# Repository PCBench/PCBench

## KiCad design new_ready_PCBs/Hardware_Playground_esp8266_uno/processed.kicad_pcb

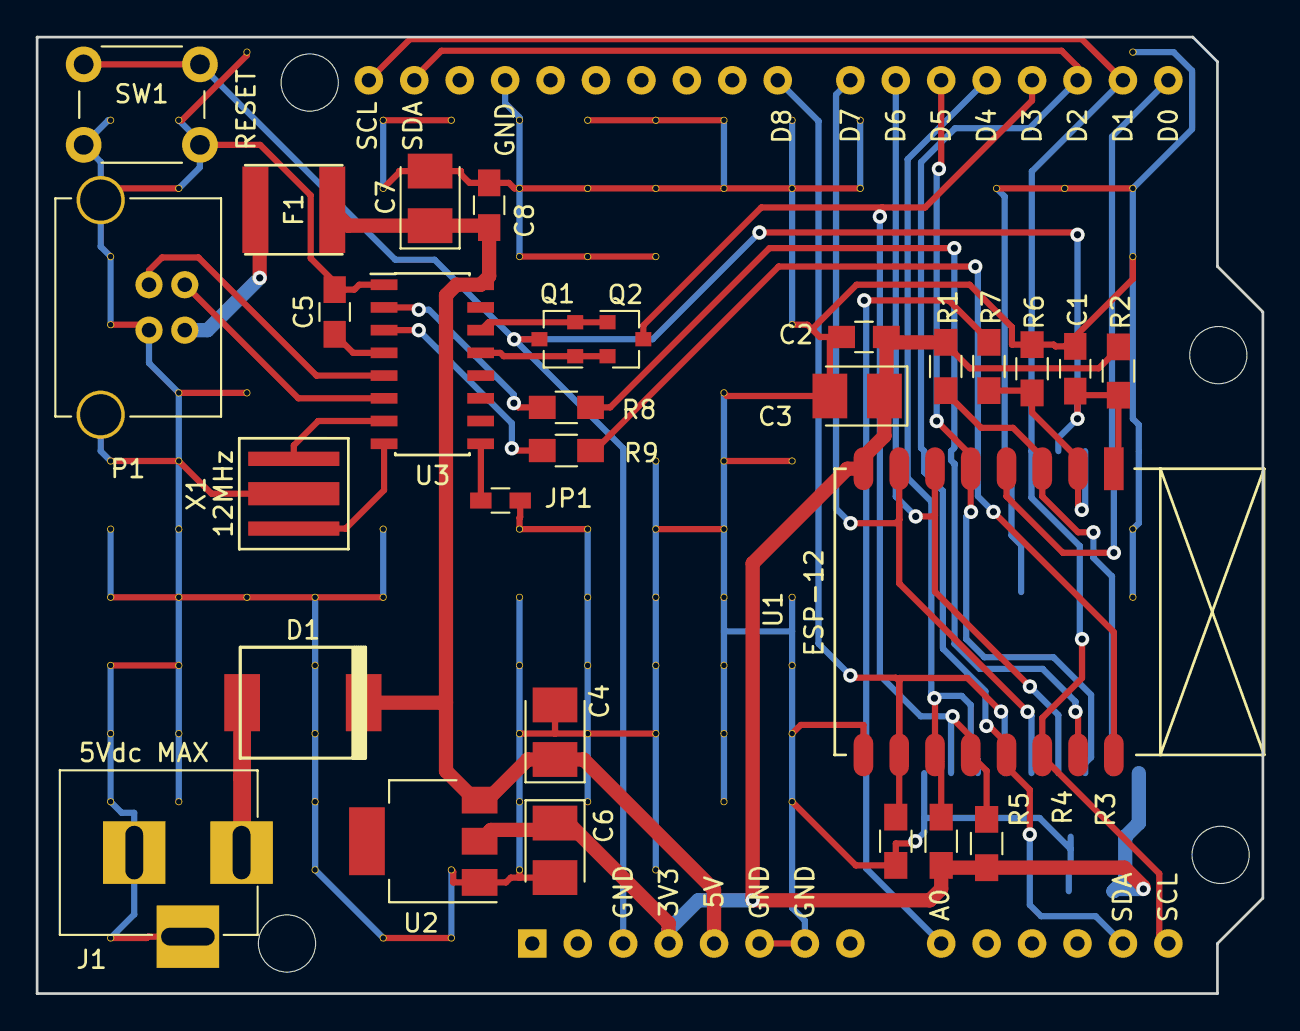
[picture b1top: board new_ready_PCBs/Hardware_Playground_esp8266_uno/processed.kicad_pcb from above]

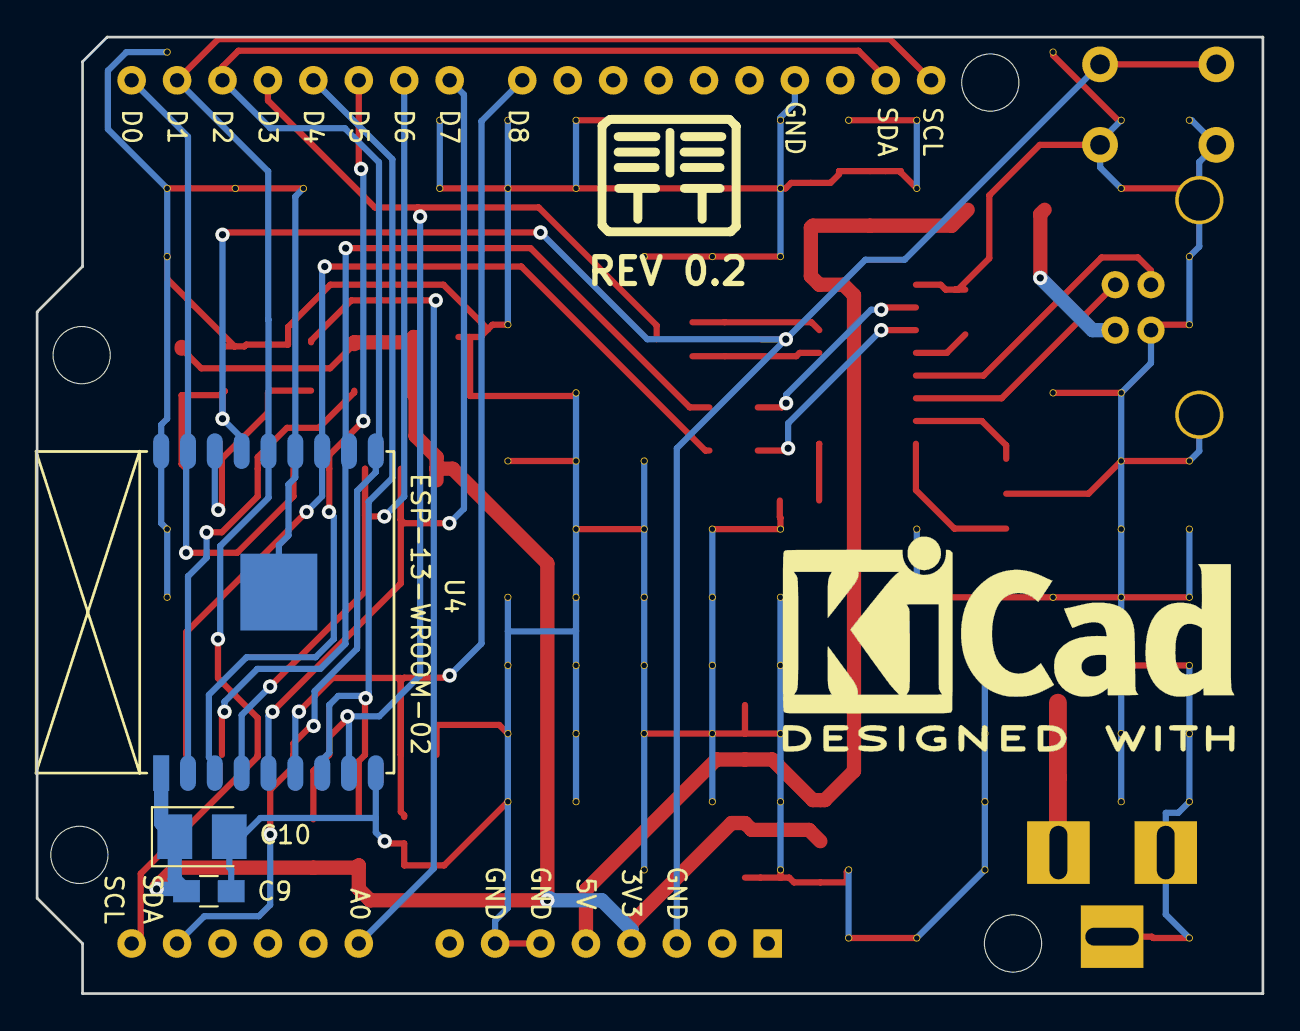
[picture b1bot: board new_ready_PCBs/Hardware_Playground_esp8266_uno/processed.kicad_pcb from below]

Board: 2 copper layers, 68.5 x 53.5 mm, 120 parts (4 on the bottom side), 30 nets.

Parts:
A1: Arduino_UNO_R3
C1, C2, C8, C9: 100n; C_0805_HandSoldering
C3, C7, C10: 10u; CP_Tantalum_Case-B_EIA-3528-21_Reflow
C4, C6: 22u; CP_Tantalum_Case-B_EIA-3528-21_Reflow
C5: 10n; C_0805_HandSoldering
D1: SS34; do214ab
F1: MF-SMDF050; mf-smdf050
J1: Barrel_Jack; BARREL_JACK
JP1: CTS; R_0603_HandSoldering
P1: USB; USB_B
Q1, Q2: 2N2222; SOT-23
R1, R2, R3, R4, R5: 10K; R_0805_HandSoldering
R6: 100K; R_0805_HandSoldering
R7: 220K; R_0805_HandSoldering
R8, R9: 470; R_0805_HandSoldering
SW1: RESET; SW_PUSH_6mm
U1: ESP-12
U2: AMS1117-3.3; SOT-223
U3: CH340G; SOIC-16_3.9x9.9mm_Pitch1.27mm
U4: ESP-13-WROOM-02
V3_2, V3_4, V3_5, V3_7, V3_8, V3_9, V3_10, V3_11, V3_12, V3_14, V4_2, V4_3, V4_6, V4_7, V4_8, V4_9, V4_10, V4_11, V4_12, V5_1, V5_6, V5_9, V6_9, V6_10, V6_11, V6_12, V6_13, V7_2, V7_3, V7_8, V7_9, V7_14, V8_2, V8_13, V8_14, V9_2, V9_3, V9_4, V9_8, V9_9, V9_10, V9_11, V9_12, V9_13, V10_2, V10_3, V10_4, V10_8, V10_9, V10_10, V10_11, V10_12, V11_2, V11_3, V11_4, V11_7, V11_8, V11_9, V11_10, V11_11, V11_13, V12_2, V12_3, V12_6, V12_7, V12_8, V12_9, V12_10, V12_11, V12_12, V13_2, V13_3, V13_5, V13_7, V13_9, V13_10, V13_11, V13_12, V14_2, V14_3, V16_3, V17_3, V18_1, V18_3, V18_4, V18_8, V18_9: AUTO_VIA; VIA_MATRIX
X1: 12MHz; ZTTCS-3

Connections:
+3V3: A1.4, C2.2, C3.1, C6.1, C9.2, C10.1, R1.2, R2.2, R3.2, R4.2, U1.8, U2.2, U4.1
+5V: A1.5, C4.1, C7.1, C8.2, D1.1, F1.1, U2.3, U3.16
/A0: A1.9, R7.1
/ADC: R6.1, R7.2, U1.2, U4.16
/DTR: Q1.1, Q2.2, U3.13
/EN: R1.1, U1.3, U4.2
/GPIO0: A1.18, Q2.3, R3.1, U1.12, U4.8
/GPIO2: A1.19, R4.1, U1.11, U4.7
/GPIO4: A1.13, A1.17, A1.31, U1.13, U4.10
/GPIO5: A1.14, A1.16, A1.32, U1.14, U4.14
/GPIO12: A1.21, U1.6, U4.4
/GPIO13: A1.22, U1.7, U4.5
/GPIO14: A1.20, U1.5, U4.3
/GPIO15: A1.23, R5.1, U1.10, U4.6
/GPIO16: A1.15, U1.4, U4.17
/RESET: A1.3, C1.2, Q1.3, R2.1, SW1.1, U1.1, U4.15
/RTS: Q1.2, Q2.1, U3.14
/RX: R8.2, U1.15, U4.11
/TX: R9.2, U1.16, U4.12
GND: A1.6, A1.7, A1.29, C1.1, C2.1, C3.2, C4.2, C5.2, C6.2, C7.2, C8.1, C9.1, C10.2, J1.2, J1.3, JP1.1, P1.4, P1.5, R5.2, R6.2, SW1.2, U1.9, U2.1, U3.1, U4.9, U4.13, U4.18, U4.PAD, V3_2.1, V3_4.1, V3_5.1, V3_7.1, V3_8.1, V3_9.1, V3_10.1, V3_11.1, V3_12.1, V3_14.1, V4_2.1, V4_3.1, V4_6.1, V4_7.1, V4_8.1, V4_9.1, V4_10.1, V4_11.1, V4_12.1, V5_1.1, V5_6.1, V5_9.1, V6_9.1, V6_10.1, V6_11.1, V6_12.1, V6_13.1, V7_2.1, V7_3.1, V7_8.1, V7_9.1, V7_14.1, V8_2.1, V8_13.1, V8_14.1, V9_2.1, V9_3.1, V9_4.1, V9_8.1, V9_9.1, V9_10.1, V9_11.1, V9_12.1, V9_13.1, V10_2.1, V10_3.1, V10_4.1, V10_8.1, V10_9.1, V10_10.1, V10_11.1, V10_12.1, V11_2.1, V11_3.1, V11_4.1, V11_7.1, V11_8.1, V11_9.1, V11_10.1, V11_11.1, V11_13.1, V12_2.1, V12_3.1, V12_6.1, V12_7.1, V12_8.1, V12_9.1, V12_10.1, V12_11.1, V12_12.1, V13_2.1, V13_3.1, V13_5.1, V13_7.1, V13_9.1, V13_10.1, V13_11.1, V13_12.1, V14_2.1, V14_3.1, V16_3.1, V17_3.1, V18_1.1, V18_3.1, V18_4.1, V18_8.1, V18_9.1, X1.2
unnamed: C5.1, U3.4
unnamed: D1.2, J1.1
unnamed: F1.2, P1.1
unnamed: JP1.2, U3.9
unnamed: P1.2, U3.6
unnamed: P1.3, U3.5
unnamed: R8.1, U3.2
unnamed: R9.1, U3.3
unnamed: U3.7, X1.1
unnamed: U3.8, X1.3

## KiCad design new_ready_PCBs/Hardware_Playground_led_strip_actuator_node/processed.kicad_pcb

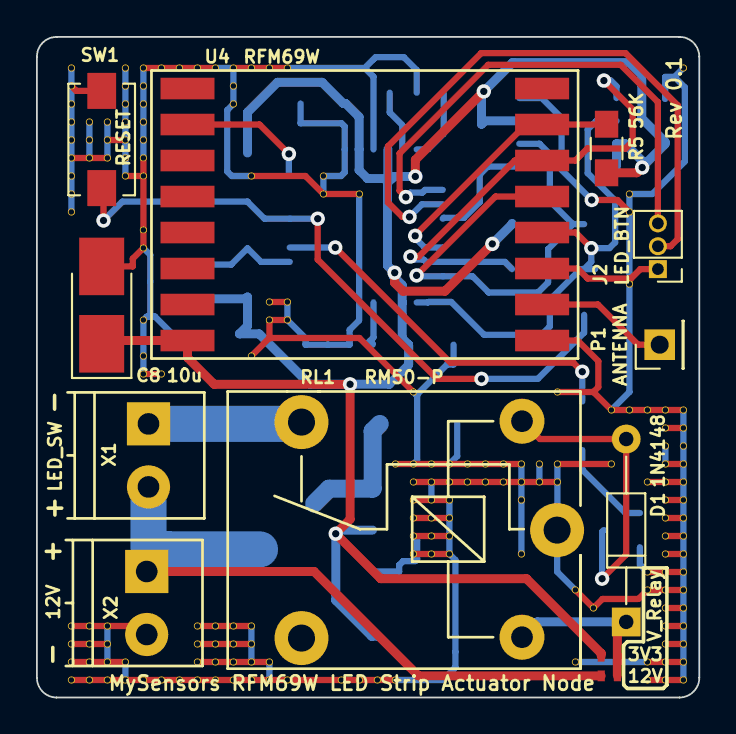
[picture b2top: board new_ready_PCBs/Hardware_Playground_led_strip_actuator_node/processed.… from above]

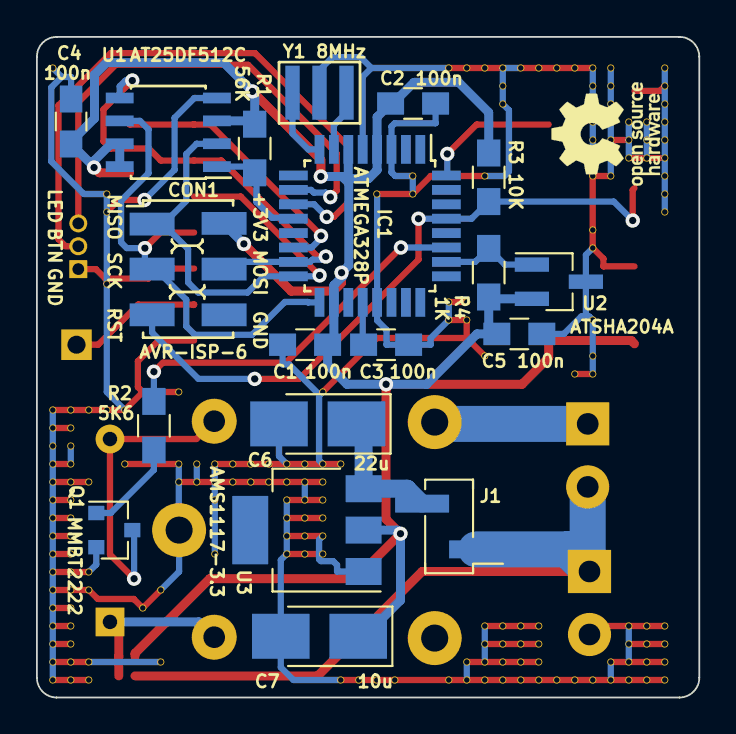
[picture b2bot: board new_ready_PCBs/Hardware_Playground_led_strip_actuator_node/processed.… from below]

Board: 2 copper layers, 36.8 x 36.7 mm, 208 parts (19 on the bottom side), 23 nets.

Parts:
C1, C2, C3, C4, C5: 100n; C_0805_HandSoldering
C6: 22u; CP_Tantalum_Case-B_EIA-3528-21_Hand
C7, C8: 10u; CP_Tantalum_Case-B_EIA-3528-21_Hand
CON1: AVR-ISP-6; AVR_ISP_SMT_Small_02x03
D1: 1N4148; D_DO-35_SOD27_P10.16mm_Horizontal
IC1: ATMEGA328P; TQFP-32_7x7mm_Pitch0.8mm
J1: EXT_DC_DC; Pin_Header_Straight_1x02_Pitch2.54mm_SMD_Pin1Left
J2: LED_BTN; Pin_Header_Straight_1x03_Pitch1.27mm
JP1: 3V3; R_0402_NoSilk
JP2: 12V; R_0402_NoSilk
P1: ANTENNA; Pin_Header_Straight_1x01_Pitch2.54mm
Q1: MMBT2222; SOT-23
R1, R5: 56K; R_0805_HandSoldering
R2: 5K6; R_0805_HandSoldering
R3: 10K; R_0805_HandSoldering
R4: 1K; R_0805_HandSoldering
RL1: RM50-P; RM50_P
SW1: RESET; SW_SPST_EVQPE1
U1: AT25DF512C; SOIC-8_3.9x4.9mm_Pitch1.27mm
U2: ATSHA204A; SOT-23_Handsoldering
U3: AMS1117-3.3; SOT-223
U4: RFM69W; RFM69HW_SMD_Handsoldering
V2_10, V2_11, V2_12, V2_13, V2_14, V2_15, V2_16, V2_17, V2_18, V2_41, V2_42, V2_43, V2_44, V3_13, V3_14, V3_15, V3_41, V3_42, V3_43, V3_44, V4_13, V4_14, V4_15, V4_41, V4_42, V4_43, V4_44, V5_10, V5_11, V5_12, V5_13, V5_14, V5_15, V5_16, V5_43, V5_44, V6_10, V6_11, V6_12, V6_13, V6_14, V6_15, V6_16, V6_19, V6_20, V6_24, V6_26, V6_27, V6_44, V7_10, V7_27, V7_44, V8_10, V8_44, V9_10, V9_41, V9_42, V9_43, V9_44, V10_10, V10_41, V10_42, V10_43, V10_44, V11_10, V11_11, V11_12, V11_41, V11_42, V11_43, V11_44, V12_10, V12_16, V12_26, V12_41, V12_42, V12_43, V12_44, V13_10, V13_23, V13_24, V13_43, V13_44, V14_10, V14_23, V14_24, V14_44, V16_16, V16_17, V17_44, V18_17, V18_44, V19_44, V20_32, V20_44, V21_28, V21_32, V21_33, V21_34, V21_35, V21_36, V21_37, V22_32, V22_33, V22_34, V22_35, V22_36, V22_37, V23_32, V23_33, V23_34, V23_35, V23_36, V23_37, V24_32, V24_33, V25_32, V25_33, V26_32, V26_33, V27_32, V27_33, V27_34, V27_37, V28_32, V28_33, V29_28, V29_32, V29_33, V30_39, V30_43, V31_40, V32_29, V32_32, V33_17, V33_18, V33_22, V33_29, V34_29, V34_33, V34_38, V34_39, V34_43, V34_44, V35_29, V35_30, V35_31, V35_32, V35_33, V35_34, V35_35, V35_36, V35_37, V35_38, V35_39, V35_40, V35_41, V35_42, V35_43, V35_44, V36_10, V36_29, V36_30, V36_31, V36_32, V36_33, V36_34, V36_35, V36_36, V36_37, V36_38, V36_39, V36_40, V36_41, V36_42, V36_43, V36_44: AUTO_VIA; VIA_MATRIX
X1: LED_SW; TerminalBlock_Pheonix_PT-3.5mm_2pol
X2: 12V; TerminalBlock_Pheonix_PT-3.5mm_2pol
Y1: 8MHz; ZTTCR-3

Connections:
+3V3: C1.2, C2.2, C4.1, C5.1, C7.1, C8.1, CON1.2, IC1.4, IC1.6, IC1.18, JP1.1, R1.2, R3.1, R4.2, R5.2, U1.3, U1.7, U1.8, U2.2, U3.2, U4.8
/ATSHA204A: IC1.26, R4.1, U2.1
/LED_12V: J1.1, JP2.2, X1.2, X2.1
/LED_BTN: IC1.11, J2.2
/LED_BTN_SIGNALING: IC1.10, J2.3
/LED_RELAY_CMD: IC1.27, R2.2
/MISO: CON1.1, IC1.16, U1.2, U4.13
/MOSI: CON1.4, IC1.15, U1.5, U4.14
/RFM69W_INT: IC1.32, U4.2
/RFM69W_SS: IC1.14, R5.1, U4.15
/RST: CON1.5, IC1.29, R3.2, SW1.1
/SCK: CON1.3, IC1.17, U1.6, U4.12
/SPI_FLASH_SS: IC1.12, R1.1, U1.1
GND: C1.1, C2.1, C3.1, C4.2, C5.2, C6.2, C7.2, C8.2, IC1.3, IC1.5, IC1.21, J2.1, Q1.2, RL1.11, SW1.2, U1.4, U2.3, U3.1, U4.9, U4.11, V2_10.1, V2_11.1, V2_12.1, V2_13.1, V2_14.1, V2_15.1, V2_16.1, V2_17.1, V2_18.1, V2_41.1, V2_42.1, V2_43.1, V2_44.1, V3_13.1, V3_14.1, V3_15.1, V3_41.1, V3_42.1, V3_43.1, V3_44.1, V4_13.1, V4_14.1, V4_15.1, V4_41.1, V4_42.1, V4_43.1, V4_44.1, V5_10.1, V5_11.1, V5_12.1, V5_13.1, V5_14.1, V5_15.1, V5_16.1, V5_43.1, V5_44.1, V6_10.1, V6_11.1, V6_12.1, V6_13.1, V6_14.1, V6_15.1, V6_16.1, V6_19.1, V6_20.1, V6_24.1, V6_26.1, V6_27.1, V6_44.1, V7_10.1, V7_27.1, V7_44.1, V8_10.1, V8_44.1, V9_10.1, V9_41.1, V9_42.1, V9_43.1, V9_44.1, V10_10.1, V10_41.1, V10_42.1, V10_43.1, V10_44.1, V11_10.1, V11_11.1, V11_12.1, V11_41.1, V11_42.1, V11_43.1, V11_44.1, V12_10.1, V12_16.1, V12_26.1, V12_41.1, V12_42.1, V12_43.1, V12_44.1, V13_10.1, V13_23.1, V13_24.1, V13_43.1, V13_44.1, V14_10.1, V14_23.1, V14_24.1, V14_44.1, V16_16.1, V16_17.1, V17_44.1, V18_17.1, V18_44.1, V19_44.1, V20_32.1, V20_44.1, V21_28.1, V21_32.1, V21_33.1, V21_34.1, V21_35.1, V21_36.1, V21_37.1, V22_32.1, V22_33.1, V22_34.1, V22_35.1, V22_36.1, V22_37.1, V23_32.1, V23_33.1, V23_34.1, V23_35.1, V23_36.1, V23_37.1, V24_32.1, V24_33.1, V25_32.1, V25_33.1, V26_32.1, V26_33.1, V27_32.1, V27_33.1, V27_34.1, V27_37.1, V28_32.1, V28_33.1, V29_28.1, V29_32.1, V29_33.1, V30_39.1, V30_43.1, V31_40.1, V32_29.1, V32_32.1, V33_17.1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
unnamed: C3.2, IC1.20
unnamed: C6.1, J1.2, U3.3
unnamed: D1.1, JP1.2, JP2.1, RL1.A1
unnamed: D1.2, Q1.3, RL1.A2
unnamed: IC1.7, Y1.3
unnamed: IC1.8, Y1.1
unnamed: P1.1, U4.10
unnamed: Q1.1, R2.1
unnamed: RL1.14, X1.1

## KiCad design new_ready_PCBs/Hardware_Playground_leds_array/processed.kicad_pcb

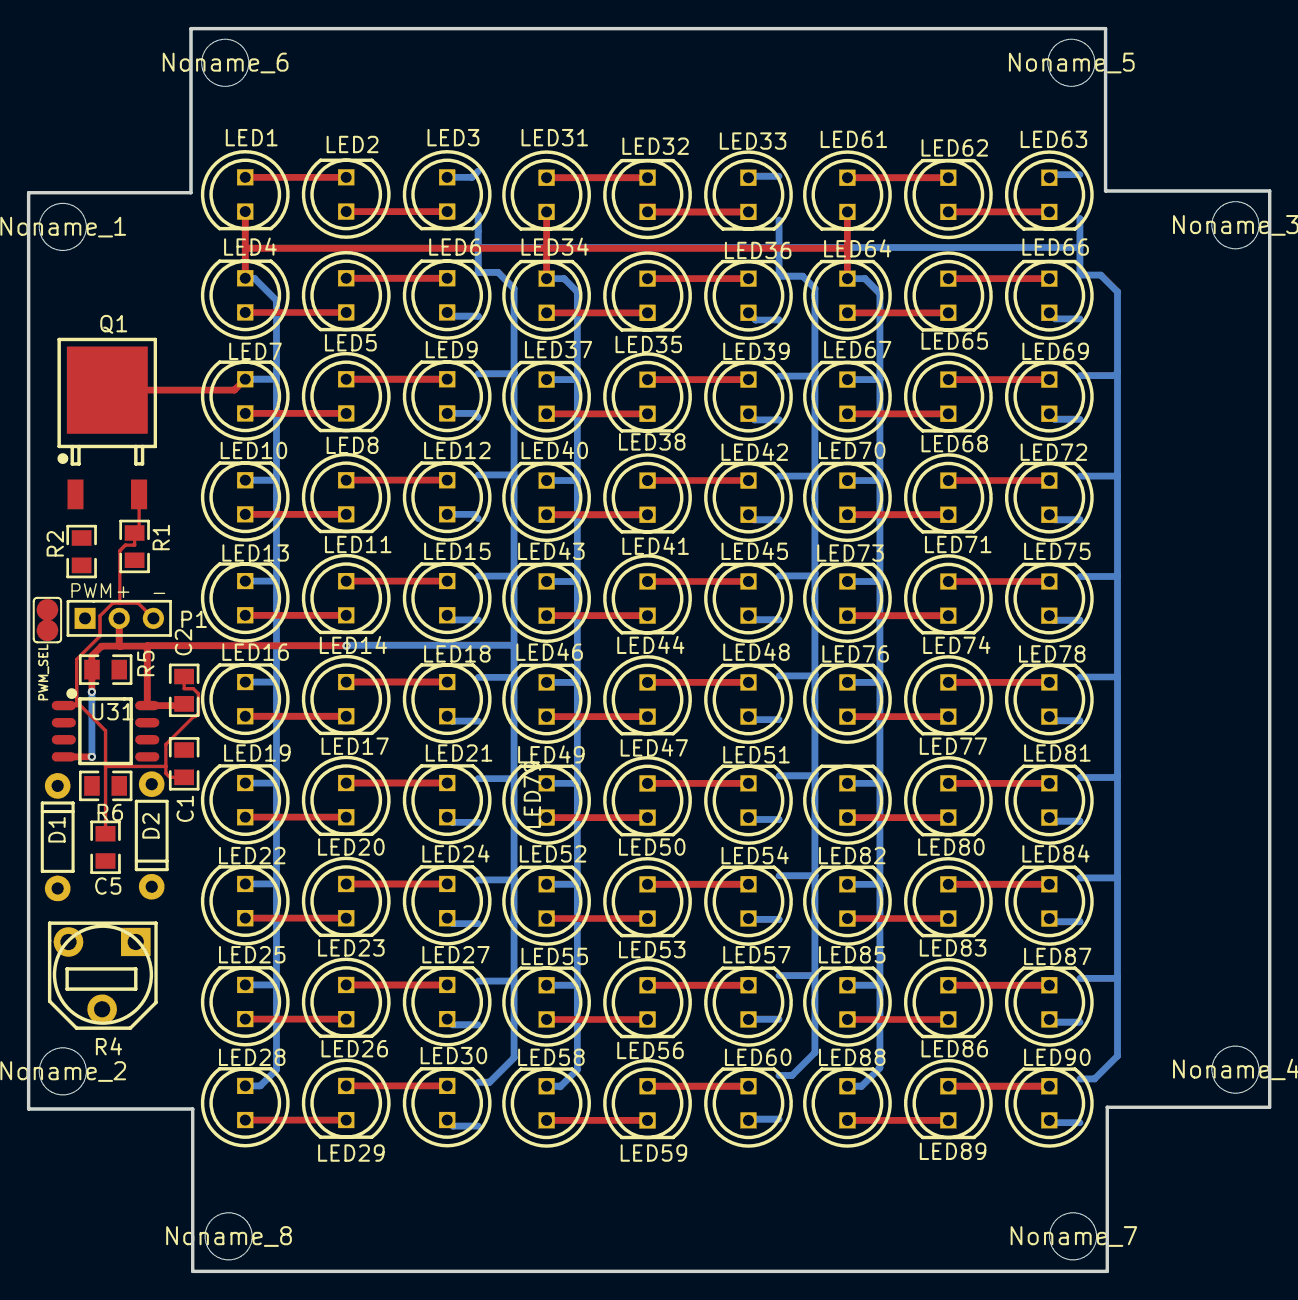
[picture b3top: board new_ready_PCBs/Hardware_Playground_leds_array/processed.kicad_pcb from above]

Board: 2 copper layers, 92.2 x 92.3 mm, 142 parts (0 on the bottom side), 93 nets.

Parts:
C1, C2: 100n; 0805
C5: 1n; 0805
D1, D2: 1N4148TA; DO-35
LED1, LED2, LED3, LED4, LED5, LED6, LED7, LED8, LED9, LED10, LED11, LED12, LED13, LED14, LED15, LED16, LED17, LED18, LED19, LED20, LED21, LED22, LED23, LED24, LED25, LED26, LED27, LED28, LED29, LED30, LED31, LED32, LED33, LED34, LED35, LED36, LED37, LED38, LED39, LED40, LED41, LED42, LED43, LED44, LED45, LED46, LED47, LED48, LED49, LED50, LED51, LED52, LED53, LED54, LED55, LED56, LED57, LED58, LED59, LED60, LED61, LED62, LED63, LED64, LED65, LED66, LED67, LED68, LED69, LED70, LED71, LED72, LED73, LED74, LED75, LED76, LED77, LED78, LED79, LED80, LED81, LED82, LED83, LED84, LED85, LED86, LED87, LED88, LED89, LED90: 5AG3HT01 280-450; LED-5MM
Noname_1, Noname_2, Noname_3, Noname_4, Noname_5, Noname_6, Noname_7, Noname_8: MountingHole_3.50mm
P1: Header-Female-2.54_1x3; HDR-3X1_2.54
PWM_SEL: SJ
Q1: IRLR024NTRPBF; TO-252-2
R1: 10K; 0805
R2: 100; 0805
R4: 10K; RM065-V1
R5, R6: 1K; 0805
U1, U2, U3, U4, U5, U6, U7, U8, U9, U10, U11, U12, U13, U14, U15, U16, U17, U18, U19, U20, U21, U22, U23, U24, U25, U26, U27, U28, U29, U30: NSI45020T1G; SOD-123F
U31: NE555G-S08-R; SOP-8_150MIL

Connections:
A: C2.1, P1.2, R5.2, U1.1, U2.1, U3.1, U4.1, U5.1, U6.1, U7.1, U8.1, U9.1, U10.1, U11.1, U12.1, U13.1, U14.1, U15.1, U16.1, U17.1, U18.1, U19.1, U20.1, U21.1, U22.1, U23.1, U24.1, U25.1, U26.1, U27.1, U28.1, U29.1, U30.1, U31.4, U31.8
GND: C1.1, C2.2, C5.1, P1.3, Q1.3, R1.1, U31.1
K: LED1.2, LED4.2, LED7.2, LED10.2, LED13.2, LED16.2, LED19.2, LED22.2, LED25.2, LED28.2, LED31.2, LED34.2, LED37.2, LED40.2, LED43.2, LED46.2, LED49.2, LED52.2, LED55.2, LED58.2, LED61.2, LED64.2, LED67.2, LED70.2, LED73.2, LED76.2, LED79.2, LED82.2, LED85.2, LED88.2, Q1.4
LED1_1: LED1.1, LED2.2
LED2_1: LED2.1, LED3.2
LED3_1: LED3.1, U1.2
LED4_1: LED4.1, LED5.2
LED5_1: LED5.1, LED6.2
LED6_1: LED6.1, U2.2
LED7_1: LED7.1, LED8.2
LED8_1: LED8.1, LED9.2
LED9_1: LED9.1, U3.2
LED10_1: LED10.1, LED11.2
LED11_1: LED11.1, LED12.2
LED12_1: LED12.1, U4.2
LED13_1: LED13.1, LED14.2
LED14_1: LED14.1, LED15.2
LED15_1: LED15.1, U5.2
LED16_1: LED16.1, LED17.2
LED17_1: LED17.1, LED18.2
LED18_1: LED18.1, U6.2
LED19_1: LED19.1, LED20.2
LED20_1: LED20.1, LED21.2
LED21_1: LED21.1, U7.2
LED22_1: LED22.1, LED23.2
LED23_1: LED23.1, LED24.2
LED24_1: LED24.1, U8.2
LED25_1: LED25.1, LED26.2
LED26_1: LED26.1, LED27.2
LED27_1: LED27.1, U9.2
LED28_1: LED28.1, LED29.2
LED29_1: LED29.1, LED30.2
LED30_1: LED30.1, U10.2
LED31_1: LED31.1, LED32.2
LED32_1: LED32.1, LED33.2
LED33_1: LED33.1, U11.2
LED34_1: LED34.1, LED35.2
LED35_1: LED35.1, LED36.2
LED36_1: LED36.1, U12.2
LED37_1: LED37.1, LED38.2
LED38_1: LED38.1, LED39.2
LED39_1: LED39.1, U13.2
LED40_1: LED40.1, LED41.2
LED41_1: LED41.1, LED42.2
LED42_1: LED42.1, U14.2
LED43_1: LED43.1, LED44.2
LED44_1: LED44.1, LED45.2
LED45_1: LED45.1, U15.2
LED46_1: LED46.1, LED47.2
LED47_1: LED47.1, LED48.2
LED48_1: LED48.1, U16.2
LED49_1: LED49.1, LED50.2
LED50_1: LED50.1, LED51.2
LED51_1: LED51.1, U17.2
LED52_1: LED52.1, LED53.2
LED53_1: LED53.1, LED54.2
LED54_1: LED54.1, U18.2
LED55_1: LED55.1, LED56.2
LED56_1: LED56.1, LED57.2
LED57_1: LED57.1, U19.2
LED58_1: LED58.1, LED59.2
LED59_1: LED59.1, LED60.2
LED60_1: LED60.1, U20.2
LED61_1: LED61.1, LED62.2
LED62_1: LED62.1, LED63.2
LED63_1: LED63.1, U21.2
LED64_1: LED64.1, LED65.2
LED65_1: LED65.1, LED66.2
LED66_1: LED66.1, U22.2
LED67_1: LED67.1, LED68.2
LED68_1: LED68.1, LED69.2
LED69_1: LED69.1, U23.2
LED70_1: LED70.1, LED71.2
LED71_1: LED71.1, LED72.2
LED72_1: LED72.1, U24.2
LED73_1: LED73.1, LED74.2
LED74_1: LED74.1, LED75.2
LED75_1: LED75.1, U25.2
LED76_1: LED76.1, LED77.2
LED77_1: LED77.1, LED78.2
LED78_1: LED78.1, U26.2
LED79_1: LED79.1, LED80.2
LED80_1: LED80.1, LED81.2
LED81_1: LED81.1, U27.2
LED82_1: LED82.1, LED83.2
LED83_1: LED83.1, LED84.2
LED84_1: LED84.1, U28.2
LED85_1: LED85.1, LED86.2
LED86_1: LED86.1, LED87.2
LED87_1: LED87.1, U29.2
LED88_1: LED88.1, LED89.2
LED89_1: LED89.1, LED90.2
LED90_1: LED90.1, U30.2

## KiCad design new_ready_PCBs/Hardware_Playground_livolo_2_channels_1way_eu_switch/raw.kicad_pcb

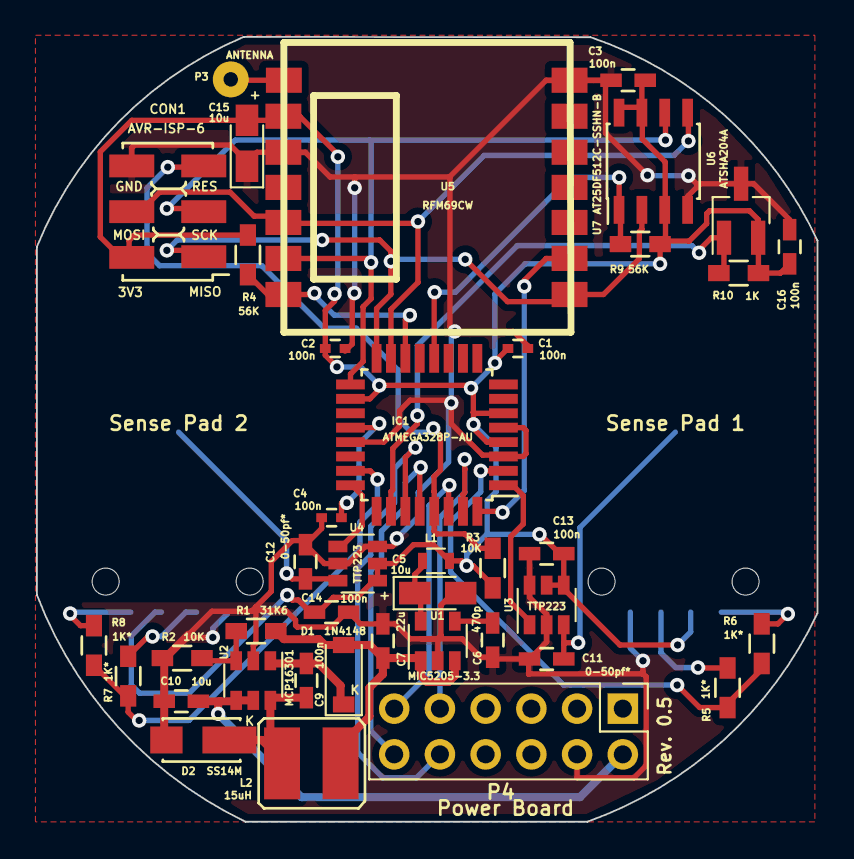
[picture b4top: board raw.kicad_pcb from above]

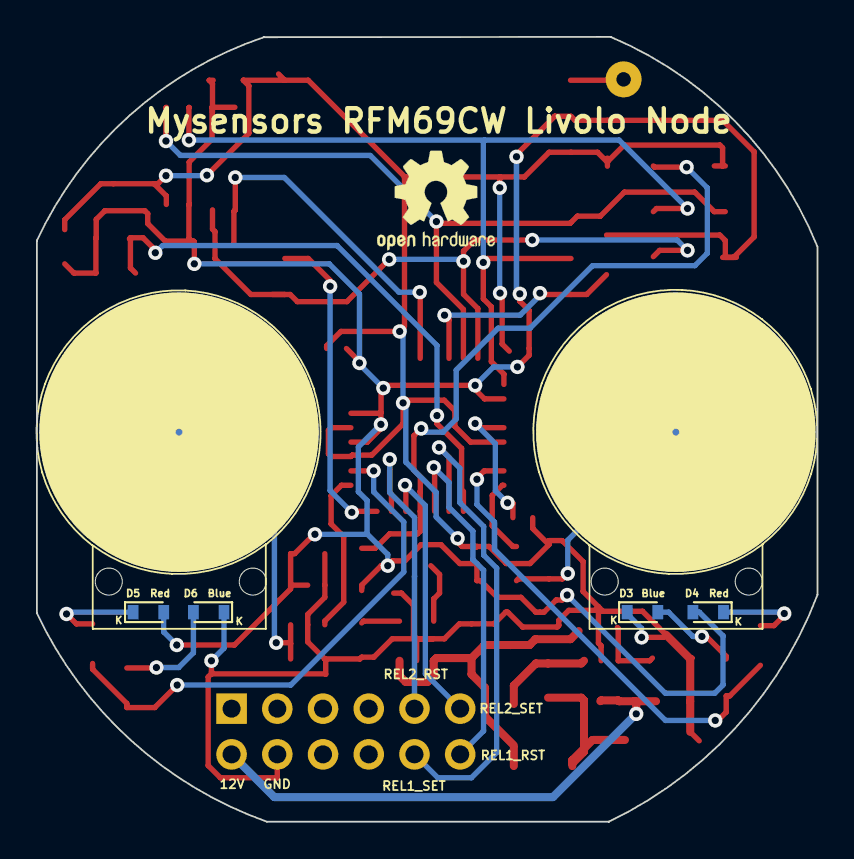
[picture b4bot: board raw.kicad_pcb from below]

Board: 2 copper layers, 43.4 x 43.6 mm, 46 parts (4 on the bottom side), 33 nets.

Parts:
C1, C2, C4: 100n; C_0402
C3, C9, C13, C14, C16: 100n; C_0603_HandSoldering
C5, C15: 10u; CP_Tantalum_Case-R_EIA-2012-12_Wave
C6: 470p; C_0603_HandSoldering
C7: 22u; C_0603_HandSoldering
C10: 10u; C_0603_HandSoldering
C11, C12: 0-50pf*; C_0603_HandSoldering
CON1: AVR-ISP-6; AVR_ISP_SMT_Small_02x03
D1: 1N4148; SOD-123
D2: SS14M
D3, D6: Blue; D_0603
D4, D5: Red; D_0603
IC1: ATMEGA328P-AU; TQFP-32_7x7mm_Pitch0.8mm
L1: BLM18HE152SN1D; R_0603
L2: 15uH; VLCF4020T-150MR68
P1: Sense Pad 1; touch_pad_16mm
P2: Sense Pad 2; touch_pad_16mm
P3: ANTENNA; SolderWirePad_single_0-8mmDrill
P4: Power Board; Pin_Header_Straight_2x06_Pitch2.54mm
R1: 31K6; R_0603_HandSoldering
R2, R3: 10K; R_0603_HandSoldering
R4, R9: 56K; R_0603_HandSoldering
R5, R6, R7, R8: 1K*; R_0603_HandSoldering
R10: 1K; R_0603_HandSoldering
U1: MIC5205-3.3; SOT-23-5
U2: MCP16301; SOT-23-6
U3, U4: TTP223; SOT-23-6
U5: RFM69CW
U6: AT25DF512C-SSHN-B; SOIC-8_3.9x4.9mm_Pitch1.27mm
U7: ATSHA204A; SOT-23_Handsoldering

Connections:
+3V3: C1.1, C2.2, C3.2, C13.1, C14.1, C15.2, C16.2, CON1.2, D4.2, D5.2, IC1.4, IC1.6, IC1.18, L1.1, R3.1, R4.2, R9.1, R10.1, U3.4, U3.5, U4.4, U4.5, U5.2, U6.3, U6.7, U6.8, U7.2
/12Vcc: C10.1, P4.2, U2.4, U2.5
/ATSHA204A: IC1.26, R10.2, U7.1
/FLASH_SS: IC1.12, R9.2, U6.1
/INT: IC1.32, U5.9
/MISO: CON1.1, IC1.16, U5.8, U6.2
/MOSI: CON1.4, IC1.15, U5.5, U6.5
/RADIO_SS: IC1.14, R4.1, U5.7
/RESET: CON1.5, IC1.29, R3.2
/Relay1_Reset: IC1.28, P4.12
/Relay1_Set: IC1.27, P4.10
/Relay2_Reset: IC1.31, P4.9
/Relay2_Set: IC1.30, P4.11
/S1_LEDs: IC1.2, R5.2, R6.2
/S2_LEDs: IC1.23, R7.2, R8.2
/SCK: CON1.3, IC1.17, U5.6, U6.6
/TS1: IC1.1, U3.1
/TS2: IC1.24, U4.1
GND: C1.2, C2.1, C3.1, C4.1, C5.2, C6.2, C7.2, C10.2, C11.2, C12.2, C13.2, C14.2, C15.1, C16.1, CON1.6, D2.2, D3.1, D6.1, IC1.3, IC1.5, IC1.21, P4.4, R2.1, U1.2, U2.2, U3.2, U3.6, U4.2, U4.6, U5.3, U5.14, U6.4, U7.3
unnamed: C4.2, IC1.20
unnamed: C5.1, L1.2, U1.5
unnamed: C6.1, U1.4
unnamed: C7.1, D1.2, L2.1, R1.2, U1.1, U1.3
unnamed: C9.1, D1.1, U2.1
unnamed: C9.2, D2.1, L2.2, U2.6
unnamed: C11.1, P1.1, U3.3
unnamed: C12.1, P2.1, U4.3
unnamed: D3.2, R7.1
unnamed: D4.1, R8.1
unnamed: D5.1, R6.1
unnamed: D6.2, R5.1
unnamed: P3.1, U5.1
unnamed: R1.1, R2.2, U2.3

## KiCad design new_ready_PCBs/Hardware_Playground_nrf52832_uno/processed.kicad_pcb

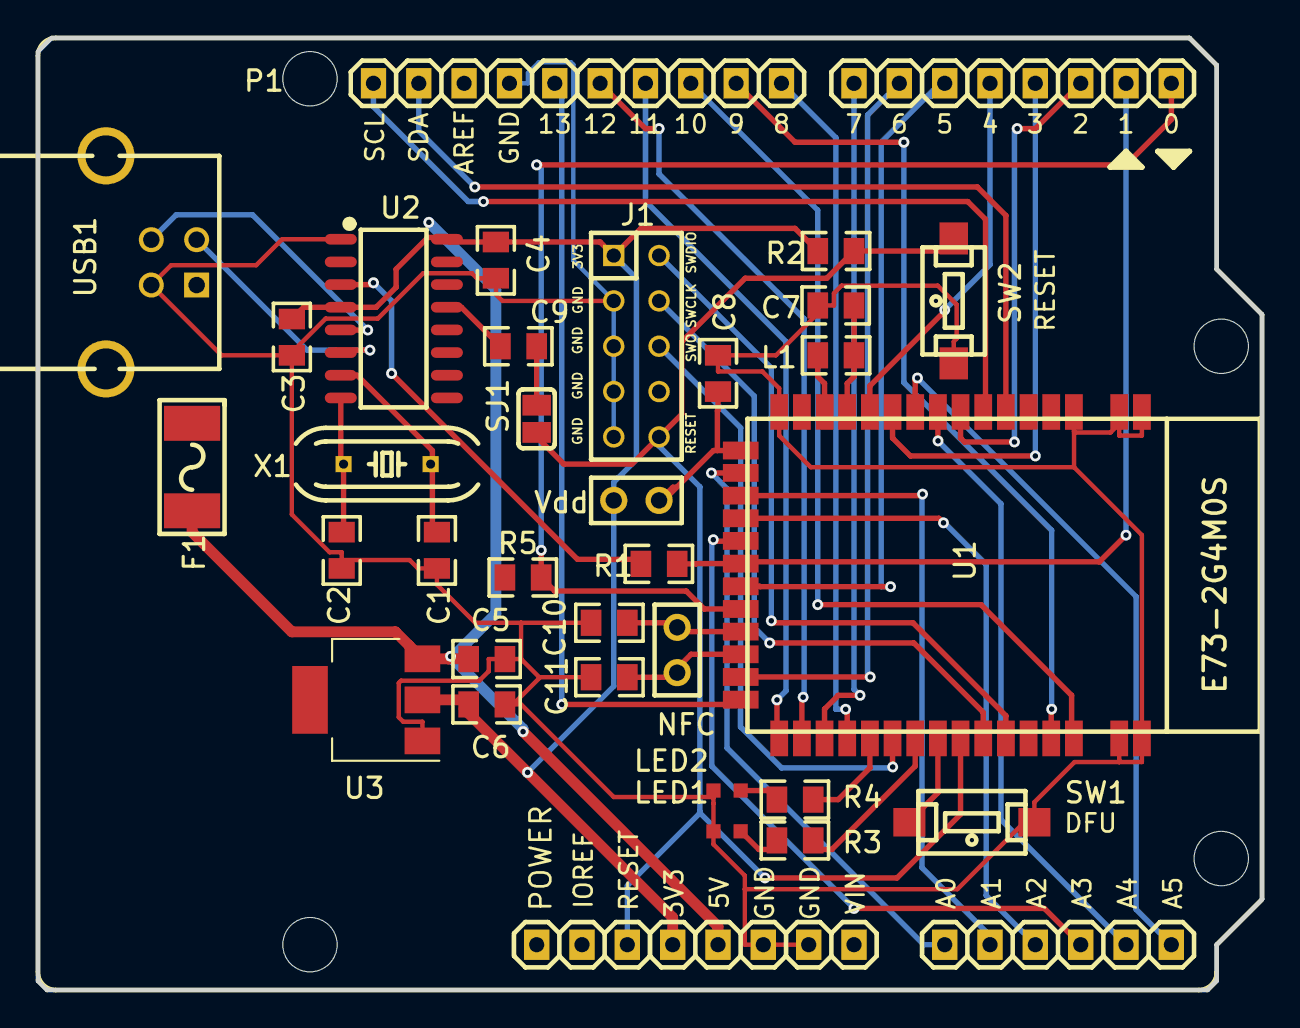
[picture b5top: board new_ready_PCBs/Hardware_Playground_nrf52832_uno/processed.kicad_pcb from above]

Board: 2 copper layers, 68.6 x 53.3 mm, 36 parts (0 on the bottom side), 46 nets.

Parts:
C1, C2: 22p; 0805
C3, C9: 10n; 0805
C4: 100n; 0805
C5, C6: 22u; 0805
C7: 1u; 0805
C8: 10u; 0805
C10, C11: 300p; 0805
DESIGNED_WITH: LOGO_EASYEDA-TOP
F1: SMD Fuse; 1808F
J1: SWD; M2X5
L1: 10uH; 0805
LED1: BLUE; CHIPLED_0603
LED2: RED; CHIPLED_0603
NFC: NFC; 1X2
Noname_1, Noname_2, Noname_3: (no value)
P1: POWER; UNO_R3
R1, R3, R4, R5: 1K; 0805
R2: 10K; 0805
SJ1: DTR; SJ
SW1: DFU; SMD-6X3.6
SW2: RESET; SMD-6X3.6
U1: E73-2G4M0S; E73-2G4M04S
U2: CH340G; SOIC-16_150MIL
U3: AMS1117-3.3; SOT-223
USB1: USB-B-Female-TH_C46393; USB-M-49
Vdd: Vdd; 1X2
X1: 12MHz; HC-49S

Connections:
+3V3: C3.1, C4.2, C6.1, J1.1, P1.28, R2.2, U2.4, U2.16, U3.2, Vdd.1
+5V: C5.1, F1.2, P1.29, U3.3
A0: P1.19, U1.17
A1: P1.20, U1.18
A2: P1.21, U1.19
A3: P1.22, U1.20
A4: P1.23, U1.8
A5: P1.24, U1.9
C9_2: C9.2, SJ1.2
D2: P1.13, U1.7
D3: P1.14, U1.10
D4: P1.15, U1.11
D5: P1.16, U1.22
D6: P1.17, U1.26
D7: P1.18, U1.30
D8: P1.1, U1.31
D9: P1.2, U1.40
D10: P1.3, U1.41
D+: U2.5, USB1.3
D-: U2.6, USB1.2
DFU: SW1.2, U1.35
DTR: C9.1, U2.13
GND: C1.1, C2.1, C3.2, C4.1, C5.2, C6.2, C7.1, C8.1, C10.2, C11.2, J1.3, J1.5, J1.7, J1.9, LED1.C, LED2.C, P1.7, P1.30, P1.31, SW1.1, SW2.1, U1.0, U1.1, U1.2, U1.15, U1.42, U1.43, U2.1, U3.1, USB1.4
MISO: P1.5, U1.29
MOSI: P1.4, U1.28
R3_1: LED1.A, R3.1
R4_1: LED2.A, R4.1
RESET: J1.10, P1.27, R2.1, SJ1.1, SW2.2, U1.36
RXD: P1.11, R5.2, U1.23
SCK: P1.6, U1.27
SCL: P1.10, U1.6
SDA: P1.9, U1.5
SWCLK: J1.4, U1.37
SWDIO: J1.2, U1.38
SWO: J1.6, U1.33
TXD: P1.12, R1.2, U1.21
U1_12: C7.2, L1.1, U1.12
U1_13: L1.2, U1.13
U1_16: C8.2, U1.16, Vdd.2
U1_24: C10.1, NFC.1, U1.24
U1_25: C11.1, NFC.2, U1.25
U1_32: R4.2, U1.32
U1_34: R3.2, U1.34
U2_3: R1.1, U2.3
U2_7: C1.2, U2.7, X1.1
U2_8: C2.2, U2.8, X1.2

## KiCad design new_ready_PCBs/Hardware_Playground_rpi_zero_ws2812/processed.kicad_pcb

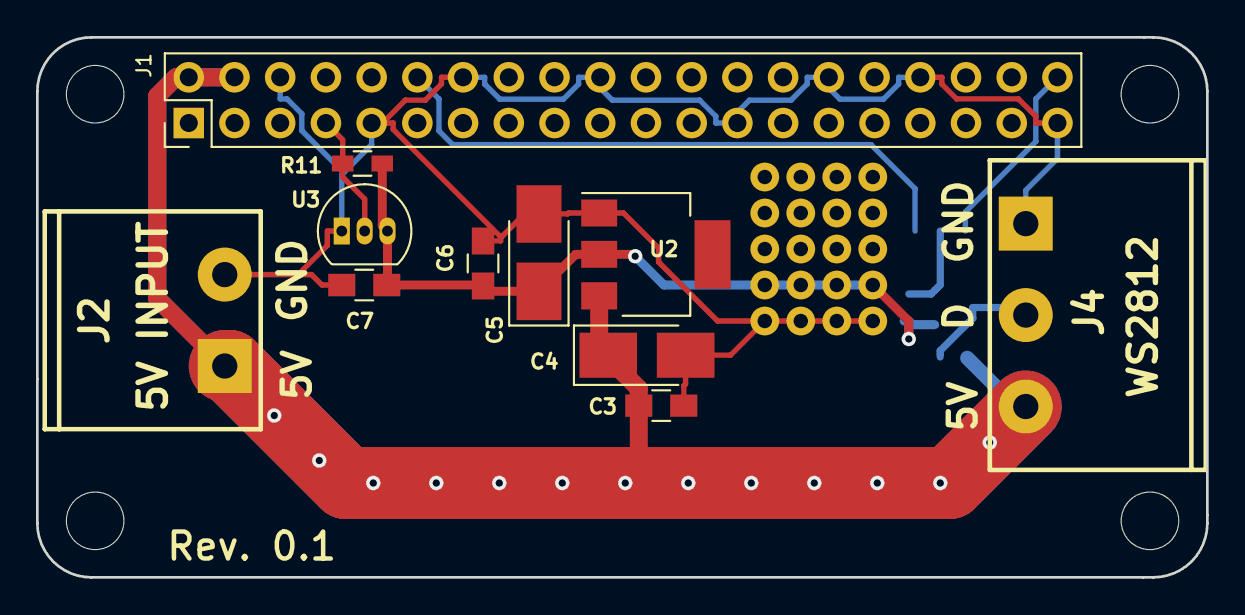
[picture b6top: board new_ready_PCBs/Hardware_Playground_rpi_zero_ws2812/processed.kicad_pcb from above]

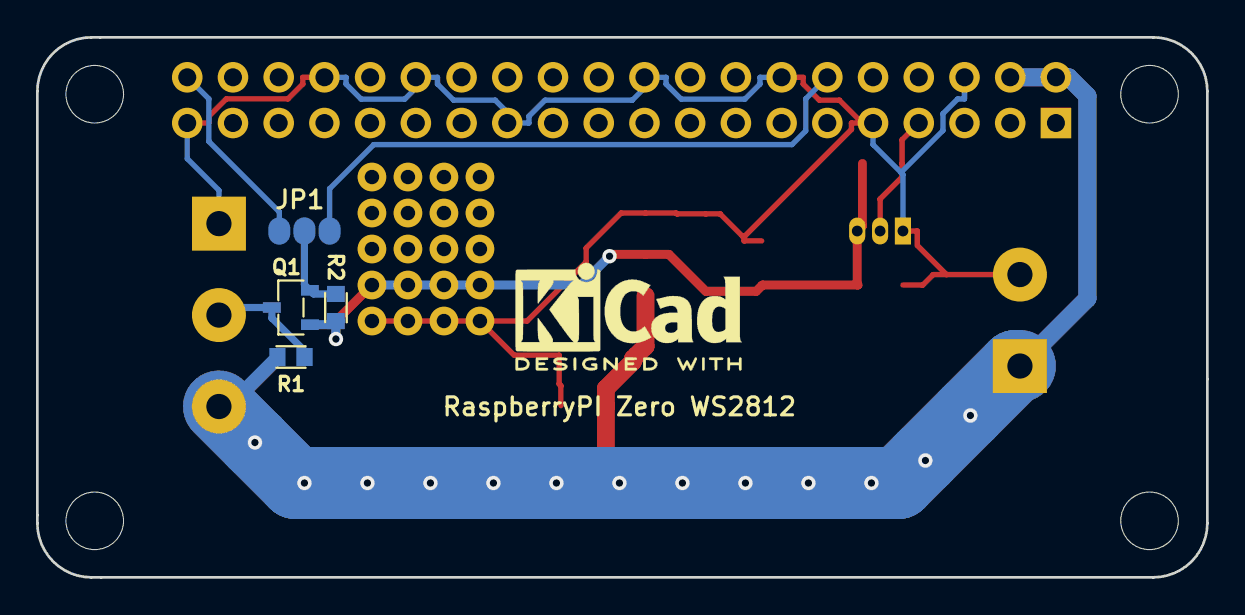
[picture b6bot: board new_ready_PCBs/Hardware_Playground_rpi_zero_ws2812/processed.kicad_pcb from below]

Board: 2 copper layers, 65.0 x 30.0 mm, 15 parts (4 on the bottom side), 8 nets.

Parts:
C3, C6, C7: 100n; C_0805_HandSoldering
C4, C5: 22u; CP_Tantalum_Case-B_EIA-3528-21_Hand
J1: RPI_Zero; Pin_Header_Straight_2x20_Pitch2.54mm
J2: 5V INPUT; mstba_2,5%2f2-g-5,08
J4: WS2812; mstba_2,5%2f3-g-5,08
JP1: ws2812_data_sel; 3_pin_solder_jumper_smd
Q1: BSS138; sot23
R1, R2: 10K; r_0603
R11: 4K7; R_0603_HandSoldering
U2: AMS1117; SOT-223
U3: DS18B20; TO-92_Inline_Narrow_Oval

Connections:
+3V3: C5.1, C6.2, C7.1, Q1.1, R2.2, R11.1, U2.2, U3.3
+5V: C3.2, C4.1, J1.2, J1.4, J2.1, J4.3, R1.1, U2.3
/TEMP_SENS: J1.7, R11.2, U3.2
/WS2812_DIN: JP1.2, Q1.3, R2.1
/WS2812_DOUT: J4.2, Q1.2, R1.2
/WS2812_PCM: J1.40, JP1.1
/WS2812_PWM: J1.12, JP1.3
GND: C3.1, C4.2, C5.2, C6.1, C7.2, J1.6, J1.9, J1.14, J1.20, J1.25, J1.30, J1.34, J1.39, J2.2, J4.1, U2.1, U3.1

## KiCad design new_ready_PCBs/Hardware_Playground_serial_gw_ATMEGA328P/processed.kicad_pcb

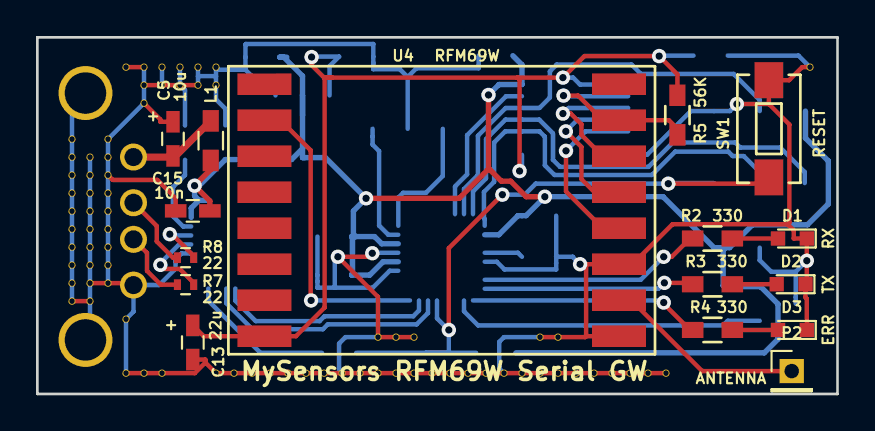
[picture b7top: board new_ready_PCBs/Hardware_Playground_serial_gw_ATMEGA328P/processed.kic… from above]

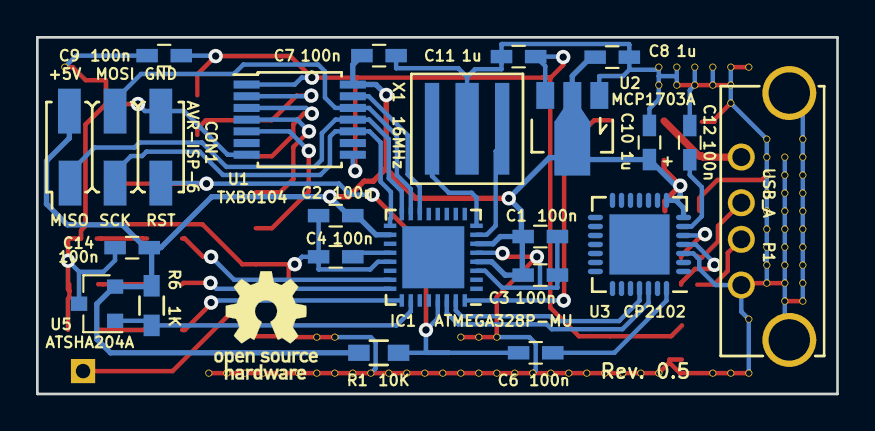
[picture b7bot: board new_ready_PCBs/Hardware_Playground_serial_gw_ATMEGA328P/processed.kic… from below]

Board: 2 copper layers, 44.5 x 19.8 mm, 114 parts (21 on the bottom side), 33 nets.

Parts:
C1, C2, C3, C4, C6, C7, C9, C12, C14: 100n; C_0603_HandSoldering
C5: 10u; C_0603_HandSoldering
C8, C10, C11: 1u; C_0603_HandSoldering
C13: 22u; C_0603_HandSoldering
C15: 10n; C_0603_HandSoldering
CON1: AVR-ISP-6; AVR_ISP_SMT_Small_02x03
D1: RX; LED_0603
D2: TX; LED_0603
D3: ERR; LED_0603
IC1: ATMEGA328P-MU; QFN-32-1EP_5x5mm_Pitch0.5mm
L1: BLM18HE152SN1D; R_0603_HandSoldering
P1: USB_A; USB_A_bottom
P2: ANTENNA; Pin_Header_Straight_1x01_Pitch2.00mm
R1: 10K; R_0603_HandSoldering
R2, R3, R4: 330; R_0603_HandSoldering
R5: 56K; R_0603_HandSoldering
R6: 1K; R_0603_HandSoldering
R7, R8: 22; R_0402
SW1: RESET; SW_SPST_EVQPE1
U1: TXB0104; TSSOP-14_4.4x5mm_Pitch0.65mm
U2: MCP1703A; SOT89-3_Housing
U3: CP2102; QFN-28-1EP_5x5mm_Pitch0.5mm
U4: RFM69W; RFM69HW_SMD_Handsoldering
U5: ATSHA204A; SOT-23
V2_7, V2_8, V2_9, V2_10, V2_11, V2_12, V2_13, V2_14, V2_15, V2_16, V3_8, V3_9, V3_10, V3_11, V3_12, V3_13, V3_14, V3_15, V3_16, V4_7, V4_8, V4_9, V4_10, V4_11, V4_12, V4_13, V4_14, V4_15, V5_3, V5_17, V5_20, V6_3, V6_4, V6_5, V6_20, V7_3, V7_4, V7_20, V8_3, V8_4, V9_3, V9_4, V10_3, V10_4, V10_20, V11_20, V12_20, V13_20, V14_20, V15_20, V16_20, V17_20, V18_20, V19_18, V19_20, V20_18, V20_20, V21_18, V21_20, V22_20, V23_20, V24_20, V25_20, V26_20, V27_20, V28_18, V28_20, V29_18, V29_20, V30_20, V31_20, V32_20, V33_20, V34_20, V35_20, V43_3: AUTO_VIA; VIA_MATRIX
X1: 16MHz; ZTTCS-3

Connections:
+3V3: C9.2, C11.1, C13.1, R5.2, U1.1, U1.8, U2.3, U4.8
+5V: C1.1, C2.2, C3.2, C7.1, C8.1, C10.2, C14.1, C15.2, CON1.2, IC1.4, IC1.6, IC1.18, L1.1, R1.1, R6.2, U1.14, U2.2, U3.7, U3.8, U5.2
/ATSHA204A: IC1.26, R6.1, U5.1
/DTR: C6.2, U3.28
/GW_ERR_LED: IC1.25, R4.2
/GW_RX_LED: IC1.23, R2.2
/GW_TX_LED: IC1.24, R3.2
/MISO: CON1.1, IC1.16, U1.11
/MOSI: CON1.4, IC1.15, U1.12
/RFM69W_INT: IC1.32, U4.2
/RFM69W_SS: IC1.14, U1.13
/RST: C6.1, CON1.5, IC1.29, R1.2, SW1.1
/SCK: CON1.3, IC1.17, U1.10
/SER_RX: IC1.31, U3.25
/SER_TX: IC1.30, U3.26
GND: C1.2, C2.1, C3.1, C4.1, C5.1, C7.2, C8.2, C9.1, C10.1, C11.2, C12.2, C13.2, C14.2, C15.1, CON1.6, D1.1, D2.1, D3.1, IC1.3, IC1.5, IC1.21, P1.4, P1.5, SW1.2, U1.7, U2.1, U3.3, U4.9, U4.11, U5.3, V2_7.1, V2_8.1, V2_9.1, V2_10.1, V2_11.1, V2_12.1, V2_13.1, V2_14.1, V2_15.1, V2_16.1, V3_8.1, V3_9.1, V3_10.1, V3_11.1, V3_12.1, V3_13.1, V3_14.1, V3_15.1, V3_16.1, V4_7.1, V4_8.1, V4_9.1, V4_10.1, V4_11.1, V4_12.1, V4_13.1, V4_14.1, V4_15.1, V5_3.1, V5_17.1, V5_20.1, V6_3.1, V6_4.1, V6_5.1, V6_20.1, V7_3.1, V7_4.1, V7_20.1, V8_3.1, V8_4.1, V9_3.1, V9_4.1, V10_3.1, V10_4.1, V10_20.1, V11_20.1, V12_20.1, V13_20.1, V14_20.1, V15_20.1, V16_20.1, V17_20.1, V18_20.1, V19_18.1, V19_20.1, V20_18.1, V20_20.1, V21_18.1, V21_20.1, V22_20.1, V23_20.1, V24_20.1, V25_20.1, V26_20.1, V27_20.1, V28_18.1, V28_20.1, V29_18.1, V29_20.1, V30_20.1, V31_20.1, V32_20.1, V33_20.1, V34_20.1, V35_20.1, V43_3.1, X1.2
unnamed: C4.2, IC1.20
unnamed: C5.2, L1.2, P1.1
unnamed: C12.1, U3.6
unnamed: D1.2, R2.1
unnamed: D2.2, R3.1
unnamed: D3.2, R4.1
unnamed: IC1.7, X1.3
unnamed: IC1.8, X1.1
unnamed: P1.2, R8.2
unnamed: P1.3, R7.2
unnamed: P2.1, U4.10
unnamed: R5.1, U1.2, U4.15
unnamed: R7.1, U3.4
unnamed: R8.1, U3.5
unnamed: U1.3, U4.14
unnamed: U1.4, U4.13
unnamed: U1.5, U4.12
